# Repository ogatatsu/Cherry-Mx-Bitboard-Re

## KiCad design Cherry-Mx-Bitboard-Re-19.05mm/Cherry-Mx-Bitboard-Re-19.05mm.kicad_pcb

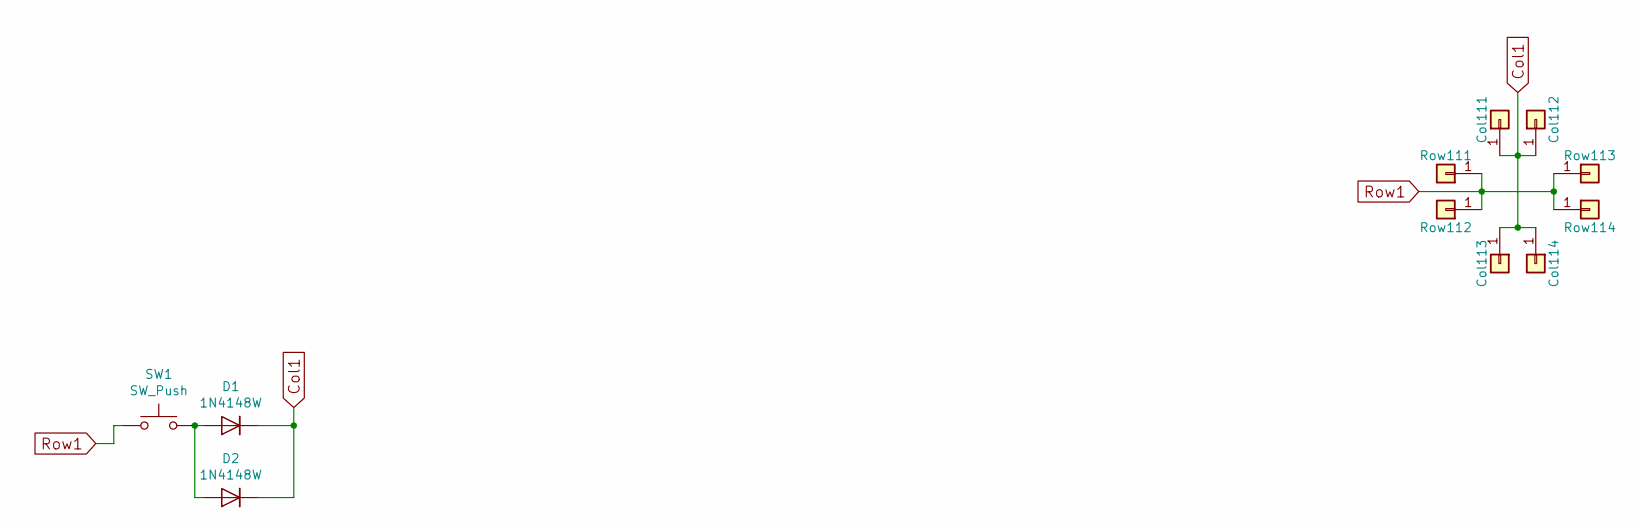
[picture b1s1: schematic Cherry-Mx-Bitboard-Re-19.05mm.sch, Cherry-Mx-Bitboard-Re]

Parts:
Col111, Col112, Col113, Col114: Conn_01x01; Wirepad
D1, D2: 1N4148W
Row111, Row112, Row113, Row114: Conn_01x01; Wirepad
SW1: SW_Push; CherryMx_Socket

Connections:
Col1: Col111.1, Col112.1, Col113.1, Col114.1, D1.1 (K), D2.1 (K)
unnamed: D1.2 (A), D2.2 (A), SW1.2
Row1: Row111.1, Row112.1, Row113.1, Row114.1, SW1.1

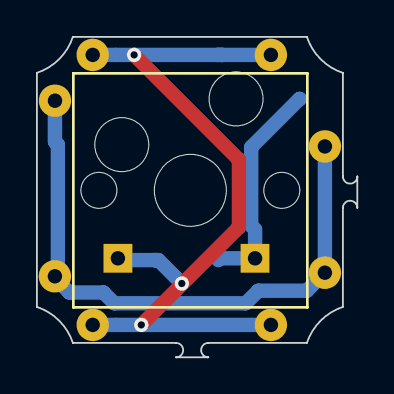
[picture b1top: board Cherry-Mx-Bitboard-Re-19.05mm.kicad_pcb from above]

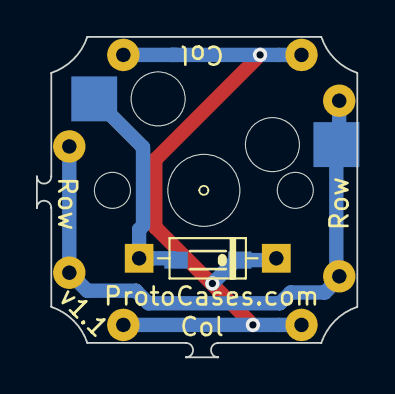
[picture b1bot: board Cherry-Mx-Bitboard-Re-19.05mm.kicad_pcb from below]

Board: 2 copper layers, 17.8 x 17.8 mm, 11 parts (10 on the bottom side), 3 nets.

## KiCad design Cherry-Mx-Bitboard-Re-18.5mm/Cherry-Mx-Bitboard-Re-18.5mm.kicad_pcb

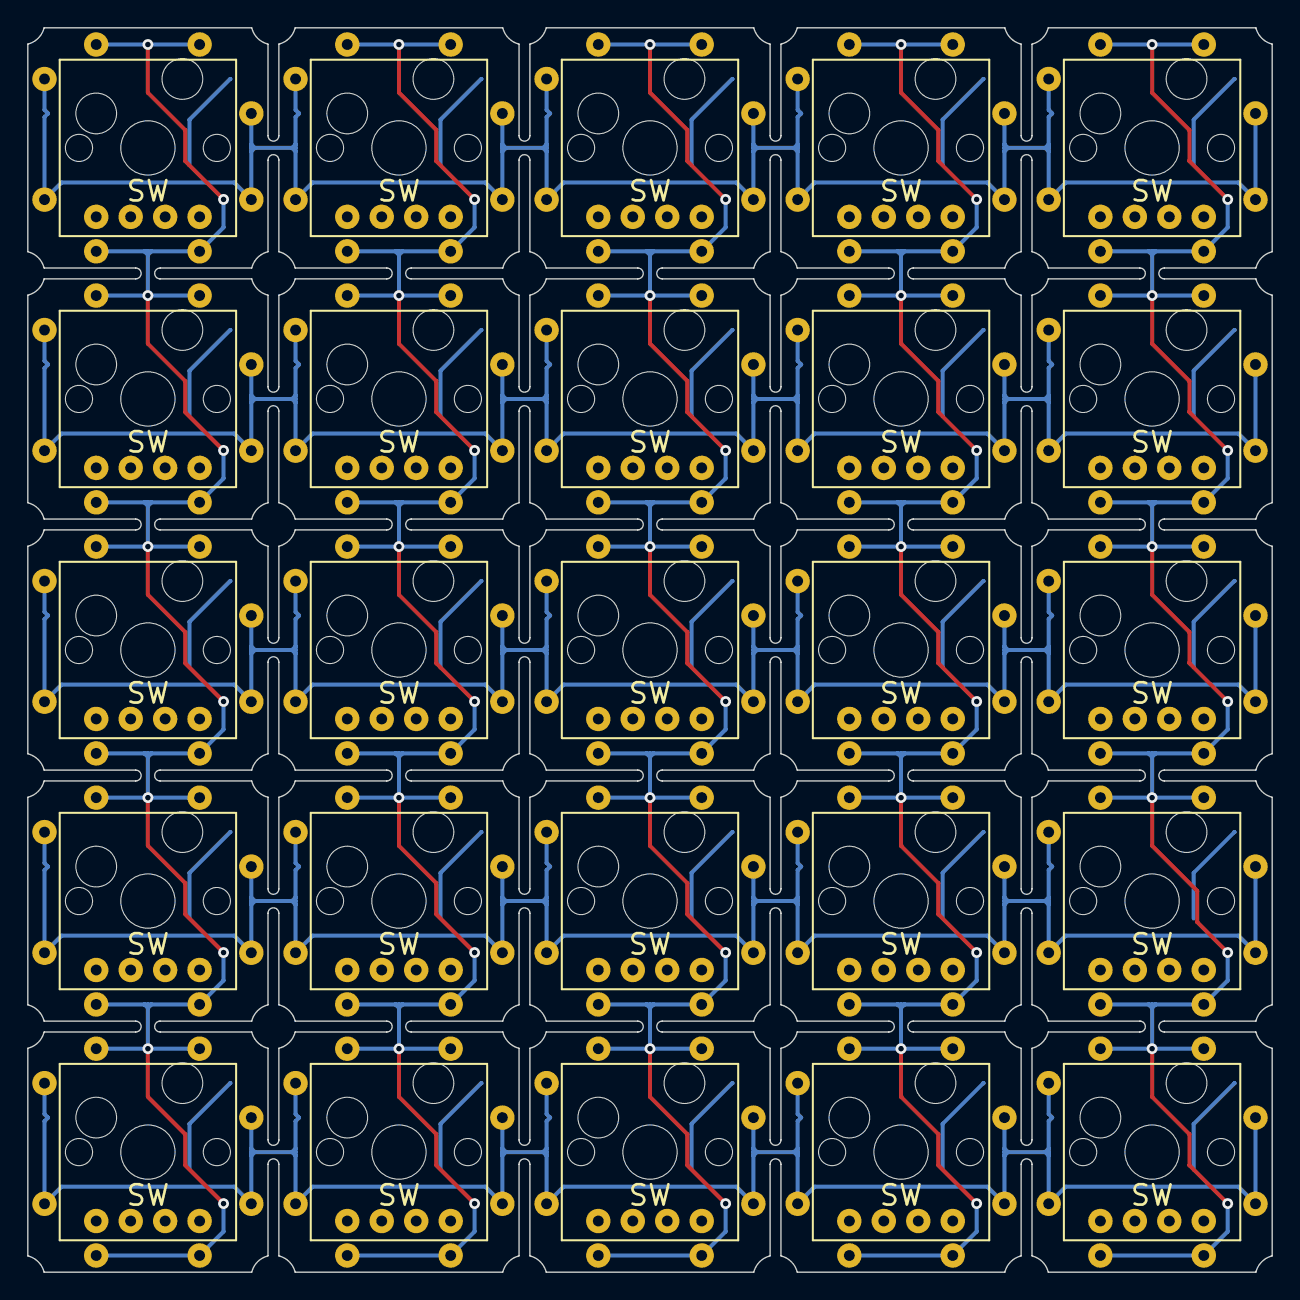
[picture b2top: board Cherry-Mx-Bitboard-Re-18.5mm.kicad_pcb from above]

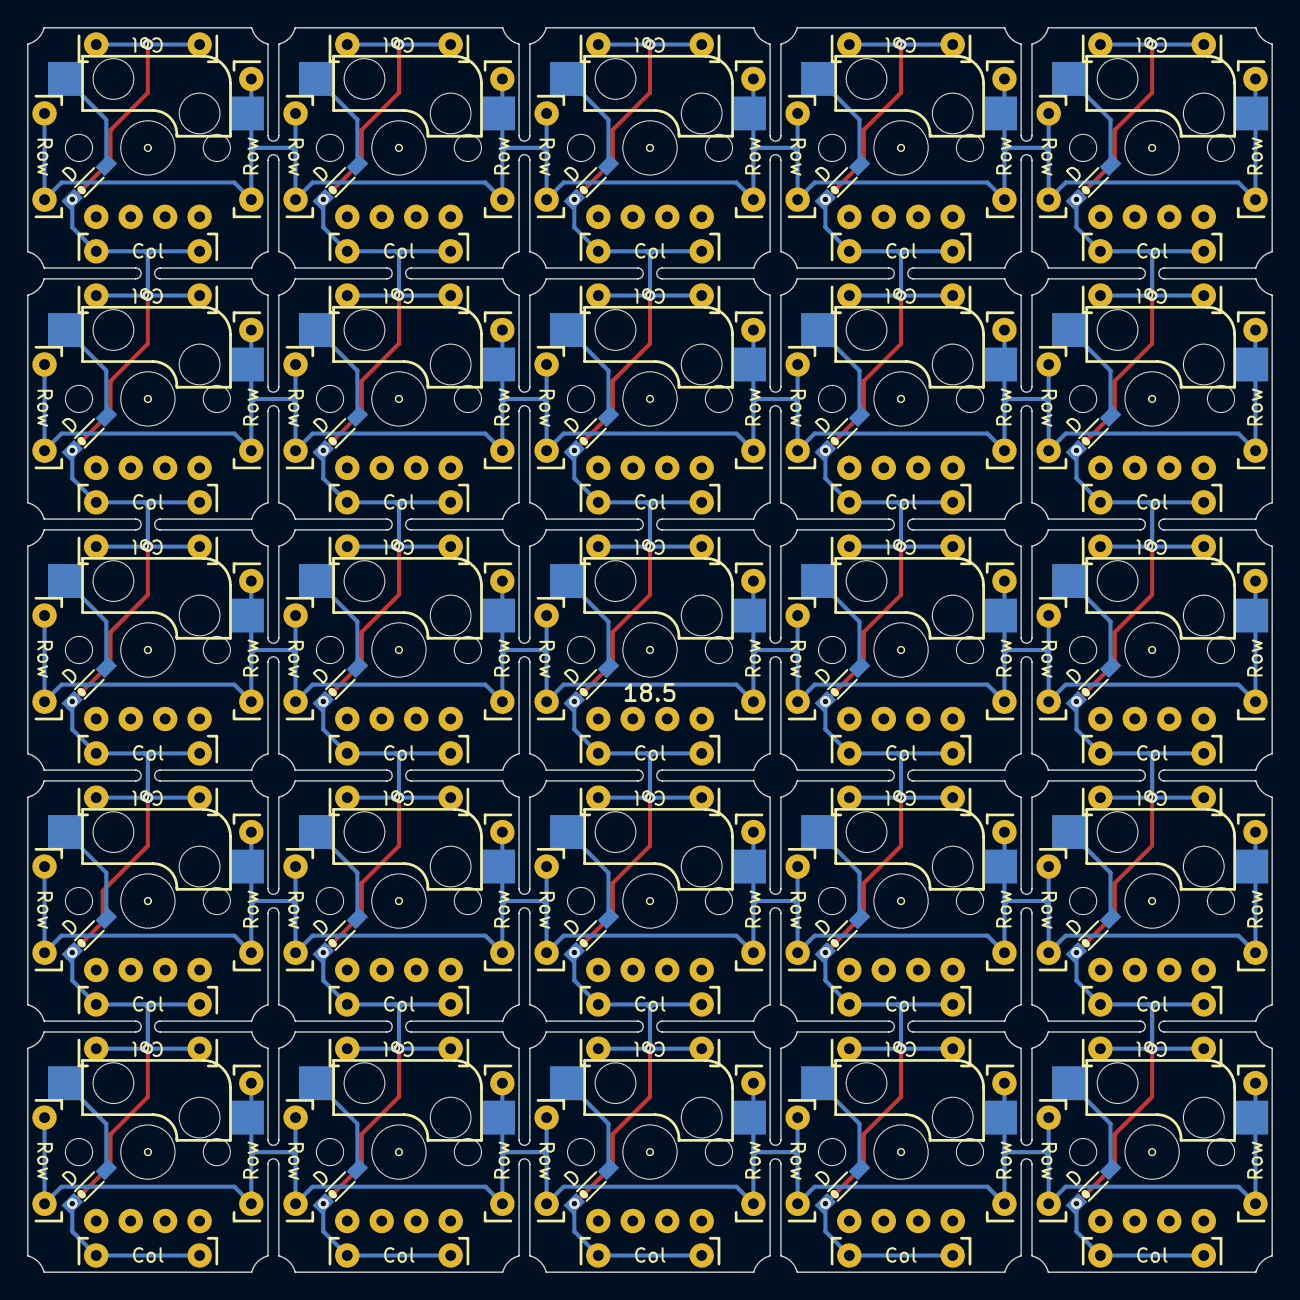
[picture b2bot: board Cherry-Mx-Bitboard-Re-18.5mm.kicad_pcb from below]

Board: 2 copper layers, 91.7 x 91.7 mm, 250 parts (225 on the bottom side), 35 nets.

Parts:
Col111, Col112, Col113, Col114, Col121, Col122, Col123, Col124, Col131, Col132, Col133, Col134, Col141, Col142, Col143, Col144, Col151, Col152, Col153, Col154, Col211, Col212, Col213, Col214, Col221, Col222, Col223, Col224, Col231, Col232, Col233, Col234, Col241, Col242, Col243, Col244, Col251, Col252, Col253, Col254, Col311, Col312, Col313, Col314, Col321, Col322, Col323, Col324, Col331, Col332, Col333, Col334, Col341, Col342, Col343, Col344, Col351, Col352, Col353, Col354, Col411, Col412, Col413, Col414, Col421, Col422, Col423, Col424, Col431, Col432, Col433, Col434, Col441, Col442, Col443, Col444, Col451, Col452, Col453, Col454, Col511, Col512, Col513, Col514, Col521, Col522, Col523, Col524, Col531, Col532, Col533, Col534, Col541, Col542, Col543, Col544, Col551, Col552, Col553, Col554: Conn_01x01; Wirepad
D1, D2, D3, D4, D5, D6, D7, D8, D9, D10, D11, D12, D13, D14, D15, D16, D17, D18, D19, D20, D21, D22, D23, D24, D25: Diode; 1N4148W
Row111, Row112, Row113, Row114, Row121, Row122, Row123, Row124, Row131, Row132, Row133, Row134, Row141, Row142, Row143, Row144, Row151, Row152, Row153, Row154, Row211, Row212, Row213, Row214, Row221, Row222, Row223, Row224, Row231, Row232, Row233, Row234, Row241, Row242, Row243, Row244, Row251, Row252, Row253, Row254, Row311, Row312, Row313, Row314, Row321, Row322, Row323, Row324, Row331, Row332, Row333, Row334, Row341, Row342, Row343, Row344, Row351, Row352, Row353, Row354, Row411, Row412, Row413, Row414, Row421, Row423, Row424, Row431, Row432, Row433, Row434, Row441, Row442, Row443, Row444, Row451, Row452, Row453, Row454, Row511, Row512, Row513, Row514, Row521, Row522, Row523, Row524, Row531, Row532, Row533, Row534, Row541, Row542, Row543, Row544, Row551, Row552, Row553, Row554: Conn_01x01; Wirepad
Rowe422: Conn_01x01; Wirepad
SW1, SW2, SW3, SW4, SW5, SW6, SW7, SW8, SW9, SW10, SW11, SW12, SW13, SW14, SW15, SW16, SW17, SW18, SW19, SW20, SW21, SW22, SW23, SW24, SW25: SW_Push; CherryMx_Socket

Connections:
Col1: Col111.1, Col112.1, Col113.1, Col114.1, Col121.1, Col122.1, Col123.1, Col124.1, Col131.1, Col132.1, Col133.1, Col134.1, Col141.1, Col142.1, Col143.1, Col144.1, Col151.1, Col152.1, Col153.1, Col154.1, D1.1, D2.1, D3.1, D4.1, D5.1
Col2: Col211.1, Col212.1, Col213.1, Col214.1, Col221.1, Col222.1, Col223.1, Col224.1, Col231.1, Col232.1, Col233.1, Col234.1, Col241.1, Col242.1, Col243.1, Col244.1, Col251.1, Col252.1, Col253.1, Col254.1, D6.1, D7.1, D8.1, D9.1, D10.1
Col3: Col311.1, Col312.1, Col313.1, Col314.1, Col321.1, Col322.1, Col323.1, Col324.1, Col331.1, Col332.1, Col333.1, Col334.1, Col341.1, Col342.1, Col343.1, Col344.1, Col351.1, Col352.1, Col353.1, Col354.1, D11.1, D12.1, D13.1, D14.1, D15.1
Col4: Col411.1, Col412.1, Col413.1, Col414.1, Col421.1, Col422.1, Col423.1, Col424.1, Col431.1, Col432.1, Col433.1, Col434.1, Col441.1, Col442.1, Col443.1, Col444.1, Col451.1, Col452.1, Col453.1, Col454.1, D16.1, D17.1, D18.1, D19.1, D20.1
Col5: Col511.1, Col512.1, Col513.1, Col514.1, Col521.1, Col522.1, Col523.1, Col524.1, Col531.1, Col532.1, Col533.1, Col534.1, Col541.1, Col542.1, Col543.1, Col544.1, Col551.1, Col552.1, Col553.1, Col554.1, D21.1, D22.1, D23.1, D24.1, D25.1
unnamed: D1.2, SW1.2
unnamed: D2.2, SW2.2
unnamed: D3.2, SW3.2
unnamed: D4.2, SW4.2
unnamed: D5.2, SW5.2
unnamed: D6.2, SW6.2
unnamed: D7.2, SW7.2
unnamed: D8.2, SW8.2
unnamed: D9.2, SW9.2
unnamed: D10.2, SW10.2
unnamed: D11.2, SW11.2
unnamed: D12.2, SW12.2
unnamed: D13.2, SW13.2
unnamed: D14.2, SW14.2
unnamed: D15.2, SW15.2
unnamed: D16.2, SW16.2
unnamed: D17.2, SW17.2
unnamed: D18.2, SW18.2
unnamed: D19.2, SW19.2
unnamed: D20.2, SW20.2
unnamed: D21.2, SW21.2
unnamed: D22.2, SW22.2
unnamed: D23.2, SW23.2
unnamed: D24.2, SW24.2
unnamed: D25.2, SW25.2
Row1: Row111.1, Row112.1, Row113.1, Row114.1, Row121.1, Row122.1, Row123.1, Row124.1, Row131.1, Row132.1, Row133.1, Row134.1, Row141.1, Row142.1, Row143.1, Row144.1, Row151.1, Row152.1, Row153.1, Row154.1, SW1.1, SW6.1, SW11.1, SW16.1, SW21.1
Row2: Row211.1, Row212.1, Row213.1, Row214.1, Row221.1, Row222.1, Row223.1, Row224.1, Row231.1, Row232.1, Row233.1, Row234.1, Row241.1, Row242.1, Row243.1, Row244.1, Row251.1, Row252.1, Row253.1, Row254.1, SW2.1, SW7.1, SW12.1, SW17.1, SW22.1
Row3: Row311.1, Row312.1, Row313.1, Row314.1, Row321.1, Row322.1, Row323.1, Row324.1, Row331.1, Row332.1, Row333.1, Row334.1, Row341.1, Row342.1, Row343.1, Row344.1, Row351.1, Row352.1, Row353.1, Row354.1, SW3.1, SW8.1, SW13.1, SW18.1, SW23.1
Row4: Row411.1, Row412.1, Row413.1, Row414.1, Row421.1, Row423.1, Row424.1, Row431.1, Row432.1, Row433.1, Row434.1, Row441.1, Row442.1, Row443.1, Row444.1, Row451.1, Row452.1, Row453.1, Row454.1, Rowe422.1, SW4.1, SW9.1, SW14.1, SW19.1, SW24.1
Row5: Row511.1, Row512.1, Row513.1, Row514.1, Row521.1, Row522.1, Row523.1, Row524.1, Row531.1, Row532.1, Row533.1, Row534.1, Row541.1, Row542.1, Row543.1, Row544.1, Row551.1, Row552.1, Row553.1, Row554.1, SW5.1, SW10.1, SW15.1, SW20.1, SW25.1

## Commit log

2019-04-21 add images
2020-01-07 start again
2020-01-07 connect everything
2020-01-07 routing
2020-01-07 move via next to col
2020-01-07 fix typo in ProtoCases.com
2020-01-07 fix pads on back
2020-01-07 remove unused kicad projects
2020-01-07 add plaque of 6 by 6
2020-01-07 try to avoid white lines on top, fail
2020-01-11 updated plaque
2020-01-11 add gerber files
2020-01-11 upload gerber
2020-01-11 fix missing holes
